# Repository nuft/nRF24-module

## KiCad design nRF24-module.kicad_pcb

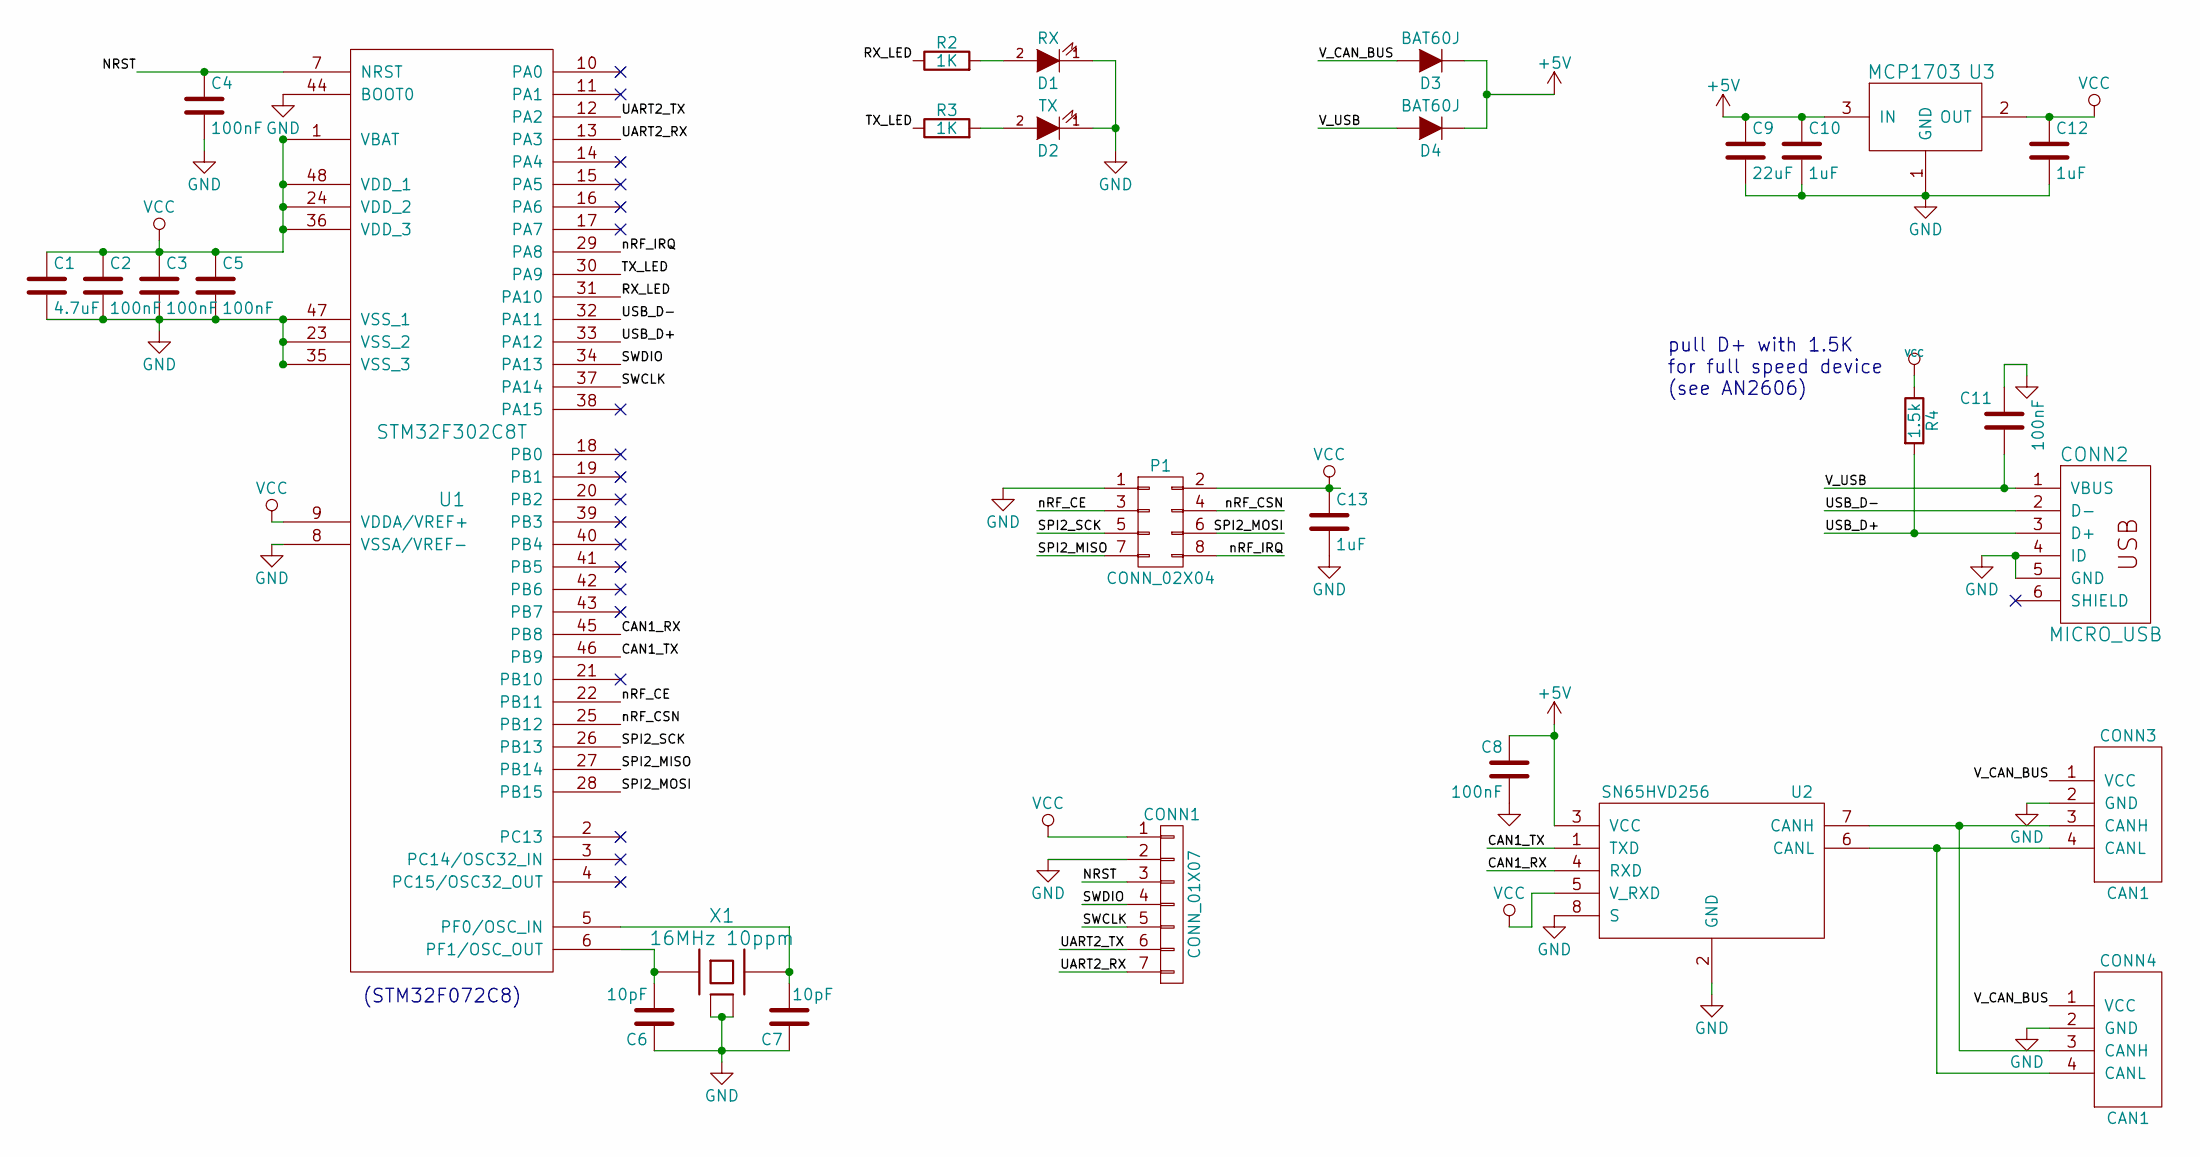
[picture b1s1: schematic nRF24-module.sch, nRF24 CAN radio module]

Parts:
C1: 4.7uF; C_0603
C2, C3, C4, C5, C8, C11: 100nF; C_0603
C6, C7: 10pF; C_0603
C9: 22uF; C_0603
C10, C12, C13: 1uF; C_0603
CONN1: CONN_01X07; Connector_Molex_PicoBlade_53047-0710
CONN2: MICRO_USB; _Micro-USB-AB-receptacle-SMT-th
CONN3, CONN4: CAN1; _Molex-PicoBlade-SMD-4
D1: RX; LED-0603
D2: TX; LED-0603
D3, D4: BAT60J; _SOD-323
P1: CONN_02X04; Pin_Header_Straight_2x04
R2, R3: 1K; R_0603
R4: 1.5k; R_0603
U1: STM32F302C8T; LQFP-48_7x7mm_Pitch0.5mm
U2: SN65HVD256; SOIC-8_3.9x4.9mm_Pitch1.27mm
U3: MCP1703; _MCP1703-SOT-23A
X1: 16MHz 10ppm; _TSX-3225-SMD-XTAL

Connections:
+5V: C8.1, C9.1, C10.1, D3.1 (K), D4.1 (K), U2.3 (VCC), U3.3 (IN)
/CAN1_RX: U1.45 (PB8), U2.4 (RXD)
/CAN1_TX: U1.46 (PB9), U2.1 (TXD)
/NRST: C4.1, CONN1.3, U1.7 (NRST)
/RX_LED: R2.1, U1.31 (PA10)
/SPI2_MISO: P1.7, U1.27 (PB14)
/SPI2_MOSI: P1.6, U1.28 (PB15)
/SPI2_SCK: P1.5, U1.26 (PB13)
/SWCLK: CONN1.5, U1.37 (PA14)
/SWDIO: CONN1.4, U1.34 (PA13)
/TX_LED: R3.1, U1.30 (PA9)
/UART2_RX: CONN1.7, U1.13 (PA3)
/UART2_TX: CONN1.6, U1.12 (PA2)
/USB_D+: CONN2.3 (D+), R4.2, U1.33 (PA12)
/USB_D-: CONN2.2 (D-), U1.32 (PA11)
/V_CAN_BUS: CONN3.1 (VCC), CONN4.1 (VCC), D3.2 (A)
/V_USB: C11.1, CONN2.1 (VBUS), D4.2 (A)
/nRF_CE: P1.3, U1.22 (PB11)
/nRF_CSN: P1.4, U1.25 (PB12)
/nRF_IRQ: P1.8, U1.29 (PA8)
GND: C1.2, C2.2, C3.2, C4.2, C5.2, C6.1, C7.1, C8.2, C9.2, C10.2, C11.2, C12.2, C13.2, CONN1.2, CONN2.4 (ID), CONN2.5 (GND), CONN3.2 (GND), CONN3.MECH (GND), CONN4.2 (GND), CONN4.MECH (GND), D1.1 (K), D2.1 (K), P1.1, U1.8 (VSSA/VREF-), U1.23 (VSS_2), U1.35 (VSS_3), U1.44 (BOOT0), U1.47 (VSS_1), U2.2 (GND), U2.8 (S), U3.1 (GND), X1.2 (case), X1.4 (case)
unnamed: C6.2, U1.6 (PF1/OSC_OUT), X1.1
unnamed: C7.2, U1.5 (PF0/OSC_IN), X1.3
unnamed: CONN3.3 (CANH), CONN4.3 (CANH), U2.7 (CANH)
unnamed: CONN3.4 (CANL), CONN4.4 (CANL), U2.6 (CANL)
unnamed: D1.2 (A), R2.2
unnamed: D2.2 (A), R3.2
VCC: C1.1, C2.1, C3.1, C5.1, C12.1, C13.1, CONN1.1, P1.2, R4.1, U1.1 (VBAT), U1.9 (VDDA/VREF+), U1.24 (VDD_2), U1.36 (VDD_3), U1.48 (VDD_1), U2.5 (V_RXD), U3.2 (OUT)

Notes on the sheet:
pull D+ with 1.5K for full speed device (see AN2606)
(STM32F072C8)

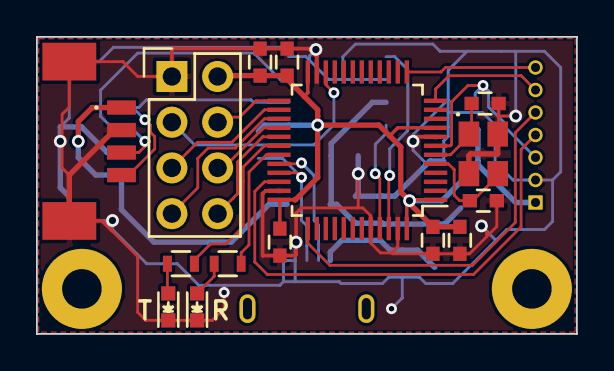
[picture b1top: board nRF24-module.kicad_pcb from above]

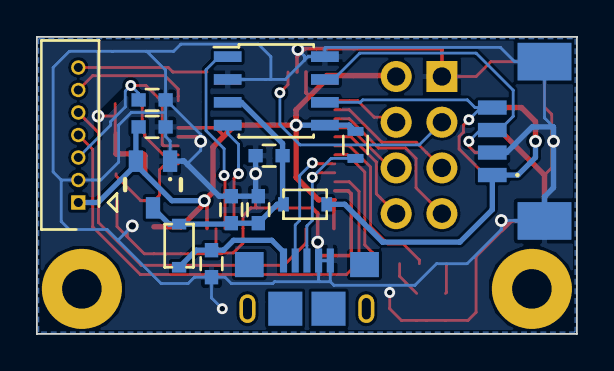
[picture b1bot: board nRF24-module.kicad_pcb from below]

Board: 2 copper layers, 30.0 x 16.5 mm, 31 parts (14 on the bottom side), 28 nets.

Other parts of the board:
_M2, _M2#2: VAL**; _M2

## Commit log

2015-11-01 start from CAN dongle as template
2015-11-04 Add kicad library submodule
2015-11-04 nRF pin assignment.
2015-11-04 No dfu pushbutton
2015-11-04 Change voltage regulator
2016-02-05 Simplify schematic
2016-02-05 Connect RX TX LEDs
2016-02-22 Start with PCB component placement
2016-03-12 Update kicad lib
2016-03-12 Routing, change pins, add debug UART
2016-03-15 Routing almost finished, add capacitor to nRF24 VCC
2016-06-04 Add mounting holes
2016-06-05 Change LED polarity, optimize routing
2016-06-05 schematic PDF
